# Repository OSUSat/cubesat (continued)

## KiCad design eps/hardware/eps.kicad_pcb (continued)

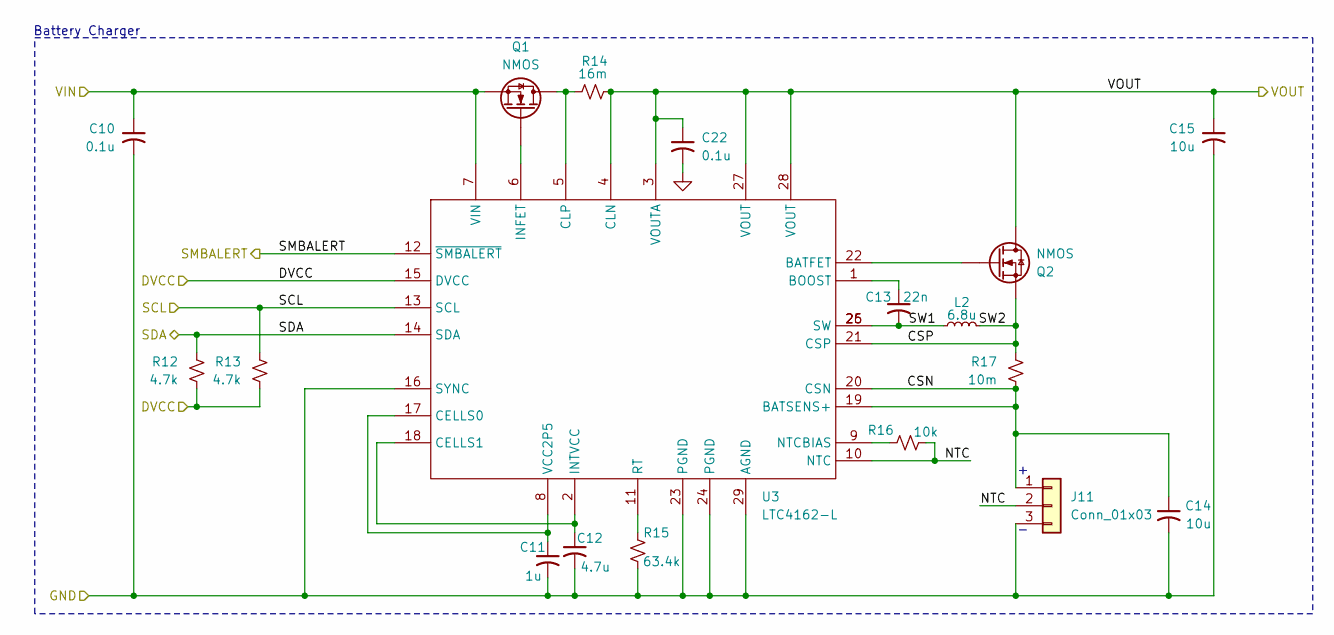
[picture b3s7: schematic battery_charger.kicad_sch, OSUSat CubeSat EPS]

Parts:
C10, C22: 0.1u; C_0402_1005Metric
C11: 1u; C_0402_1005Metric
C12: 4.7u; C_0402_1005Metric
C13: 22n; C_0402_1005Metric
C14: 10u; C_0402_1005Metric
C15: 10u; C_1206_3216Metric
J11: Conn_01x03; JST_PH_S3B-PH-K_1x03_P2.00mm_Horizontal
L2: 6.8u; L_Vishay_IHLP-2020
Q1, Q2: NMOS; TRANS_FDMC8327L
R12, R13: 4.7k; R_0402_1005Metric
R14: 16m; R_1206_3216Metric
R15: 63.4k; R_0402_1005Metric
R16: 10k; R_0402_1005Metric
R17: 10m; R_1206_3216Metric
U3: LTC4162-L; QFN-28-1EP_4x5mm_P0.5mm_EP2.65x3.65mm

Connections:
+3.3V: R12.2, R13.2, U3.15 (DVCC); also elsewhere on the board
/Battery Charger/CSN: C14.1, J11.1, R17.2, U3.19 (BATSENS+), U3.20 (CSN)
/Battery Charger/CSP: L2.2, Q2.5 (S), Q2.6 (S), Q2.7 (S), Q2.8 (S), Q2.9 (S), R17.1, U3.21 (CSP)
/Battery Charger/NTC: J11.2, R16.2, U3.10 (NTC)
/Battery Charger/SW1: C13.2, L2.1, U3.25 (SW), U3.26 (SW)
/Battery Charger/VOUT: C15.1, C22.1, Q2.1 (D), Q2.2 (D), Q2.3 (D), R14.2, U3.3 (VOUTA), U3.4 (CLN), U3.27 (VOUT), U3.28 (VOUT); also elsewhere on the board
/C1_ALERT: U3.12 (~SMBALERT); also elsewhere on the board
/C1_SCL: R13.1, U3.13 (SCL); also elsewhere on the board
/C1_SDA: R12.1, U3.14 (SDA); also elsewhere on the board
/VSYS: C10.1, Q1.5 (S), Q1.6 (S), Q1.7 (S), Q1.8 (S), Q1.9 (S), U3.7 (VIN); also elsewhere on the board
GND: C10.2, C11.2, C12.2, C14.2, C15.2, C22.2, J11.3, R15.2, U3.16 (SYNC), U3.23 (PGND), U3.24 (PGND), U3.29 (AGND); also elsewhere on the board
unnamed: Q1.4 (G), U3.6 (INFET)
unnamed: Q2.4 (G), U3.22 (BATFET)
unnamed: C13.1, U3.1 (BOOST)
unnamed: C11.1, U3.8 (VCC2P5), U3.17 (CELLS0)
unnamed: C12.1, U3.2 (INTVCC), U3.18 (CELLS1)
unnamed: Q1.1 (D), Q1.2 (D), Q1.3 (D), R14.1, U3.5 (CLP)
unnamed: R16.1, U3.9 (NTCBIAS)
unnamed: R15.1, U3.11 (RT)

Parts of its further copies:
C16, C23: 0.1u; C_0402_1005Metric
C17: 1u; C_0402_1005Metric
C18: 4.7u; C_0402_1005Metric
C19: 22n; C_0402_1005Metric
C20: 10u; C_0402_1005Metric
C21: 10u; C_1206_3216Metric
J12: Conn_01x03; JST_PH_S3B-PH-K_1x03_P2.00mm_Horizontal
L3: 6.8u; L_Vishay_IHLP-2020
Q3, Q4: NMOS; TRANS_FDMC8327L
R18, R19: 4.7k; R_0402_1005Metric
R20: 16m; R_1206_3216Metric
R21: 63.4k; R_0402_1005Metric
R22: 10k; R_0402_1005Metric
R23: 10m; R_1206_3216Metric
U4: LTC4162-L; QFN-28-1EP_4x5mm_P0.5mm_EP2.65x3.65mm

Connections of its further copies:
+3.3V: R18.2, R19.2, U4.15 (DVCC); also elsewhere on the board
/Battery Charger1/CSN: C20.1, J12.1, R23.2, U4.19 (BATSENS+), U4.20 (CSN)
/Battery Charger1/CSP: L3.2, Q4.5 (S), Q4.6 (S), Q4.7 (S), Q4.8 (S), Q4.9 (S), R23.1, U4.21 (CSP)
/Battery Charger1/NTC: J12.2, R22.2, U4.10 (NTC)
/Battery Charger1/SW1: C19.2, L3.1, U4.25 (SW), U4.26 (SW)
/Battery Charger1/VOUT: C21.1, C23.1, Q4.1 (D), Q4.2 (D), Q4.3 (D), R20.2, U4.3 (VOUTA), U4.4 (CLN), U4.27 (VOUT), U4.28 (VOUT); also elsewhere on the board
/C2_ALERT: U4.12 (~SMBALERT); also elsewhere on the board
/C2_SCL: R19.1, U4.13 (SCL); also elsewhere on the board
/C2_SDA: R18.1, U4.14 (SDA); also elsewhere on the board
/VSYS: C16.1, Q3.5 (S), Q3.6 (S), Q3.7 (S), Q3.8 (S), Q3.9 (S), U4.7 (VIN); also elsewhere on the board
GND: C16.2, C17.2, C18.2, C20.2, C21.2, C23.2, J12.3, R21.2, U4.16 (SYNC), U4.23 (PGND), U4.24 (PGND), U4.29 (AGND); also elsewhere on the board
unnamed: Q3.4 (G), U4.6 (INFET)
unnamed: Q4.4 (G), U4.22 (BATFET)
unnamed: C19.1, U4.1 (BOOST)
unnamed: C17.1, U4.8 (VCC2P5), U4.17 (CELLS0)
unnamed: C18.1, U4.2 (INTVCC), U4.18 (CELLS1)
unnamed: Q3.1 (D), Q3.2 (D), Q3.3 (D), R20.1, U4.5 (CLP)
unnamed: R22.1, U4.9 (NTCBIAS)
unnamed: R21.1, U4.11 (RT)

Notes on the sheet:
Battery Charger

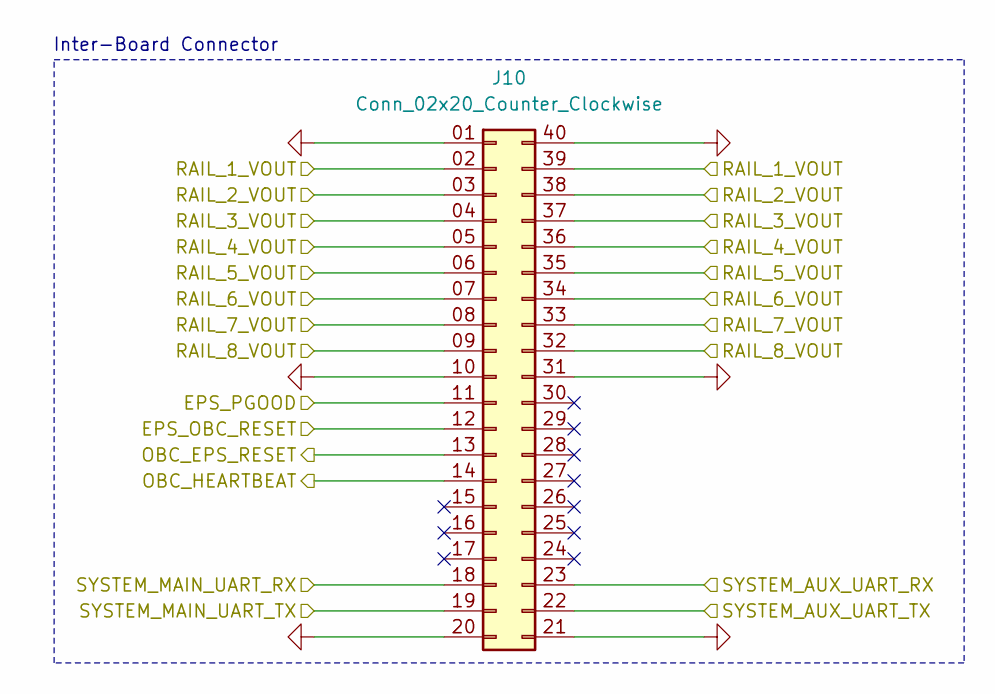
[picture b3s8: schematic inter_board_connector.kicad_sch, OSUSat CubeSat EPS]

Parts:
J10: Conn_02x20_Counter_Clockwise; SAMTEC_ERM8-020-X-X-DV

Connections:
/AUX_RX: J10.23; also elsewhere on the board
/AUX_TX: J10.22; also elsewhere on the board
/Current Monitors/RAIL_1_VOUT: J10.02 (Pin_2), J10.39; also elsewhere on the board
/Current Monitors/RAIL_2_VOUT: J10.03 (Pin_3), J10.38; also elsewhere on the board
/Current Monitors/RAIL_3_VOUT: J10.04 (Pin_4), J10.37; also elsewhere on the board
/Current Monitors/RAIL_4_VOUT: J10.05 (Pin_5), J10.36; also elsewhere on the board
/Current Monitors/RAIL_5_VOUT: J10.06 (Pin_6), J10.35; also elsewhere on the board
/Current Monitors/RAIL_6_VOUT: J10.07 (Pin_7), J10.34; also elsewhere on the board
/Current Monitors/RAIL_7_VOUT: J10.08 (Pin_8), J10.33; also elsewhere on the board
/Current Monitors/RAIL_8_VOUT: J10.09 (Pin_9), J10.32; also elsewhere on the board
/MAIN_RX: J10.18; also elsewhere on the board
/MAIN_TX: J10.19; also elsewhere on the board
/OBC_HRT: J10.14; also elsewhere on the board
/OBC_RST: J10.12; also elsewhere on the board
/PGOOD: J10.11; also elsewhere on the board
/RESET: J10.13; also elsewhere on the board
GND: J10.01 (Pin_1), J10.10, J10.20, J10.21, J10.31, J10.40; also elsewhere on the board

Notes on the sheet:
Inter-Board Connector

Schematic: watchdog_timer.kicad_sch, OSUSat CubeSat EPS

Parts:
R32: 2k; R_0402_1005Metric
U9: TPS35-Q1; SOT-23-8

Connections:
+3.3V: R32.1, U9.2 (~MR), U9.6 (WD-EN), U9.8 (VDD); also elsewhere on the board
/RESET: R32.2, U9.7 (~RESET); also elsewhere on the board
/SET0: U9.1 (SET0); also elsewhere on the board
/SET1: U9.5 (SET1); also elsewhere on the board
/WDI: U9.3 (WDI); also elsewhere on the board
GND: U9.4 (GND); also elsewhere on the board

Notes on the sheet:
The TPS3435CBHAJDDFR should be suitable.
Ensure that the open-drain RESET pin variant is selected.
Watchdog Timer

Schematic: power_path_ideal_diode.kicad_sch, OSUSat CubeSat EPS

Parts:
C133: 4.7u; C_1206_3216Metric
R119: 680k; R_0402_1005Metric
R120, R121: 100k; R_0402_1005Metric
R122, R123: 50k; R_0402_1005Metric
R124, R125, R126, R127: 470k; R_0402_1005Metric
U41: LTC4415; MSOP-16-1EP_3x4.039mm_P0.5mm_EP1.651x2.845mm

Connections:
+3.3V: R124.1, R125.1, R126.1, R127.1; also elsewhere on the board
/3v3 Voltage Regulator/VIN: C133.1, U41.9 (OUT2), U41.10 (OUT2), U41.15 (OUT1), U41.16 (OUT1); also elsewhere on the board
/Battery Charger1/VOUT: U41.7 (IN2), U41.8 (IN2); also elsewhere on the board
/Battery Charger/VOUT: R119.1, U41.1 (IN1), U41.2 (IN1); also elsewhere on the board
/D_STAT1: R124.2, U41.14 (~STAT1); also elsewhere on the board
/D_STAT2: R127.2, U41.11 (~STAT2); also elsewhere on the board
/D_WARN1: R125.2, U41.13 (~WARN1); also elsewhere on the board
/D_WARN2: R126.2, U41.12 (~WARN2); also elsewhere on the board
GND: C133.2, R121.2, R122.2, R123.2, U41.17 (GND); also elsewhere on the board
unnamed: R122.1, U41.4 (CLIM1)
unnamed: R123.1, U41.5 (CLIM2)
unnamed: R119.2, R120.1, U41.3 (EN1)
unnamed: R120.2, R121.1, U41.6 (~EN2)

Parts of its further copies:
C134: 4.7u; C_1206_3216Metric
R128: 680k; R_0402_1005Metric
R129, R130: 100k; R_0402_1005Metric
R131, R132: 50k; R_0402_1005Metric
R133, R134, R135, R136: 470k; R_0402_1005Metric
U42: LTC4415; MSOP-16-1EP_3x4.039mm_P0.5mm_EP1.651x2.845mm

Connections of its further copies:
+3.3V: R133.1, R134.1, R135.1, R136.1; also elsewhere on the board
/MPPT_V: U42.7 (IN2), U42.8 (IN2); also elsewhere on the board
/Power Path Ideal Diode1/VOUT: C134.1, U42.9 (OUT2), U42.10 (OUT2), U42.15 (OUT1), U42.16 (OUT1); also elsewhere on the board
/U_STAT1: R133.2, U42.14 (~STAT1); also elsewhere on the board
/U_STAT2: R136.2, U42.11 (~STAT2); also elsewhere on the board
/U_WARN1: R134.2, U42.13 (~WARN1); also elsewhere on the board
/U_WARN2: R135.2, U42.12 (~WARN2); also elsewhere on the board
GND: C134.2, R130.2, R131.2, R132.2, U42.17 (GND); also elsewhere on the board
unnamed: R131.1, U42.4 (CLIM1)
unnamed: R132.1, U42.5 (CLIM2)
unnamed: R128.2, R129.1, U42.3 (EN1)
unnamed: R129.2, R130.1, U42.6 (~EN2)
VBUS: R128.1, U42.1 (IN1), U42.2 (IN1); also elsewhere on the board

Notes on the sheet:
Power Path Ideal Diode

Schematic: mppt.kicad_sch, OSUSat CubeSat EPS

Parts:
C1: 47uF; C_1206_3216Metric
C2: 4.7uF; C_0402_1005Metric
C3: 1uF; C_0402_1005Metric
C4, C5: 22n; C_0402_1005Metric
C6: 4.7u; C_1206_3216Metric; Breakdown Voltage 16V
C7: 4.7u; C_0402_1005Metric; Breakdown Voltage 10V
C8, C9: 4.7u; C_0402_1005Metric; not fitted
L1: 6.8uH; L_Vishay_IHLP-2020
R10, R11: 18k; R_0402_1005Metric
U2: LTC3130-1; MSOP-16-1EP_3x4.039mm_P0.5mm_EP1.651x2.845mm

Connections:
/MPPT/MPPC: U2.8 (MPPC); also elsewhere on the board
/MPPT/VCC: C7.1, U2.7 (VCC), U2.9 (VS2)
/MPPT/VIN: C1.1, C2.1, C3.1, U2.4 (PVIN), U2.5 (VIN), U2.6 (RUN); also elsewhere on the board
/MPPT_ADC: R10.1, R11.2; also elsewhere on the board
/MPPT_V: C6.1, C8.1, C9.1, R11.1, U2.14 (VOUT); also elsewhere on the board
/PGOOD: U2.13 (PGOOD); also elsewhere on the board
GND: C1.2, C2.2, C3.2, C6.2, C7.2, C8.2, C9.2, R10.2, U2.1 (GND), U2.10 (VS1), U2.11 (MODE), U2.12 (EXTVCC), U2.17 (EPAD); also elsewhere on the board
unnamed: C4.2, U2.2 (BST1)
unnamed: C5.1, U2.15 (BST2)
unnamed: C4.1, L1.1, U2.3 (SW1)
unnamed: C5.2, L1.2, U2.16 (SW2)

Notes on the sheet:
LTC3130 Buck-Boost MPPC Controller

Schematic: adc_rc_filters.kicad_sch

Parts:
C135, C136, C137, C138, C139, C140, C141, C142, C143, C144: 100n; C_0402_1005Metric
R137, R138, R139, R140, R141, R142, R143, R144, R145, R146: 1.5k; R_0402_1005Metric

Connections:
/5V_REG_ADC: R138.1; also elsewhere on the board
/MPPT_ADC: R137.1; also elsewhere on the board
/STM32L4/5V_REG_S: C136.1, R138.2; also elsewhere on the board
/STM32L4/MPPT_S: C135.1, R137.2; also elsewhere on the board
/STM32L4/RAIL_1_S: C137.1, R139.2; also elsewhere on the board
/STM32L4/RAIL_2_S: C138.1, R140.2; also elsewhere on the board
/STM32L4/RAIL_3_S: C139.1, R141.2; also elsewhere on the board
/STM32L4/RAIL_4_S: C140.1, R142.2; also elsewhere on the board
/STM32L4/RAIL_5_S: C141.1, R143.2; also elsewhere on the board
/STM32L4/RAIL_6_S: C142.1, R144.2; also elsewhere on the board
/STM32L4/RAIL_7_S: C143.1, R145.2; also elsewhere on the board
/STM32L4/RAIL_8_S: C144.1, R146.2; also elsewhere on the board
GND: C135.2, C136.2, C137.2, C138.2, C139.2, C140.2, C141.2, C142.2, C143.2, C144.2, R139.1, R140.1, R141.1, R142.1, R143.1, R144.1, R145.1, R146.1; also elsewhere on the board

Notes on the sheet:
This gives a cutoff frequency around 1KHz
ADC RC Filters

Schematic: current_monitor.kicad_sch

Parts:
C24, C25, C29: 0.1uF; C_0402_1005Metric
C26: 1uF; C_0402_1005Metric
C27: 1uF; C_0805_2012Metric
NT1: NetTie_2; NetTie-2_SMD_Pad0.5mm
Q5, Q6: IRLML0030; SOT-23
R24, R28: 0; R_0402_1005Metric
R25: 100k; R_0402_1005Metric
R26, R27, R29: 1M; R_0402_1005Metric
TP1: TestPoint; TestPoint_Pad_D1.0mm
U5: NCS214RSQT2G; SOT-363_SC-70-6
U6: 74LVC1G07SE-7; SOT-353_SC-70-5
U7: SOT-23-6
U8: TPS22810DRVT; WSON-6-1EP_2x2mm_P0.65mm_EP1x1.6mm

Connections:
+3.3V: NT1.1, R24.1, R26.1, R27.1, R29.1, U5.3 (VS); also elsewhere on the board
/Current Monitors/OBC/RREF+: U7.5 (VREF); also elsewhere on the board
/Current Monitors/OBC/RREF-: R25.1, U7.4 (IN-); also elsewhere on the board
/Current Monitors/OBC/Shunt+: NT1.2, U5.5 (IN-); also elsewhere on the board
/Current Monitors/OBC/Shunt-: C27.2, U5.4 (IN+), U8.6 (VIN); also elsewhere on the board
/Current Monitors/RAIL_1_RST: U6.2; also elsewhere on the board
/Current Monitors/RAIL_1_VOUT: C29.2, TP1.1, U8.1 (VOUT), U8.2 (QOD); also elsewhere on the board
/STM32L4/RAIL_1_ON: R28.1, R29.2, U8.5 (EN/UVLO); also elsewhere on the board
GND: C24.2, C25.1, C26.1, C27.1, C29.1, Q5.2 (S), Q6.2 (S), R25.2, U5.1 (REF), U5.2 (GND), U5.6 (OUT), U6.3, U7.2 (VSS), U7.3 (IN+), U8.3 (CT), U8.4 (GND), U8.7 (GND); also elsewhere on the board
unnamed: Q5.3 (D), Q6.1 (G), R27.2
unnamed: C26.2, Q5.1 (G), R26.2, U6.4, U7.1
unnamed: Q6.3 (D), R28.2
unnamed: C24.1, C25.2, R24.2, U6.5, U7.6 (VDD)

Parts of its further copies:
C55, C56, C60, C63, C64, C68, C71, C72, C76, C79, C80, C84, C87, C88, C92, C95, C96, C100, C103, C104, C108: 0.1uF; C_0402_1005Metric
C57, C65, C73, C81, C89, C97, C105: 1uF; C_0402_1005Metric
C58, C66, C74, C82, C90, C98, C106: 1uF; C_0805_2012Metric
NT2, NT3, NT4, NT5, NT6, NT7, NT8: NetTie_2; NetTie-2_SMD_Pad0.5mm
Q7, Q8, Q9, Q10, Q11, Q12, Q13, Q14, Q15, Q16, Q17, Q18, Q19, Q20: IRLML0030; SOT-23
R51, R55, R59, R63, R67, R71, R75, R79, R83, R87, R91, R95, R99, R103: 0; R_0402_1005Metric
R52, R60, R68, R76, R84, R92, R100: 100k; R_0402_1005Metric
R53, R54, R56, R61, R62, R64, R69, R70, R72, R77, R78, R80, R85, R86, R88, R93, R94, R96, R101, R102, R104: 1M; R_0402_1005Metric
TP2, TP3, TP4, TP5, TP6, TP7, TP8: TestPoint; TestPoint_Pad_D1.0mm
U11, U15, U19, U23, U27, U31, U35: NCS214RSQT2G; SOT-363_SC-70-6
U12, U16, U20, U24, U28, U32, U36: 74LVC1G07SE-7; SOT-353_SC-70-5
U13, U17, U21, U25, U29, U33, U37: SOT-23-6
U14, U18, U22, U26, U30, U34, U38: TPS22810DRVT; WSON-6-1EP_2x2mm_P0.65mm_EP1x1.6mm

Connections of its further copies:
+3.3V: NT2.1, NT3.1, NT4.1, NT5.1, NT6.1, R51.1, R53.1, R54.1, R56.1, R59.1, R61.1, R62.1, R64.1, R67.1, R69.1, R70.1, R72.1, R75.1, R77.1, R78.1, R80.1, R83.1, R85.1, R86.1, R88.1, R93.1, R94.1, R96.1, R101.1, R102.1, R104.1, U11.3 (VS), U15.3 (VS), U19.3 (VS), U23.3 (VS), U27.3 (VS), U31.3 (VS), U35.3 (VS); also elsewhere on the board
+5V: NT7.1, NT8.1, R91.1, R99.1; also elsewhere on the board
/Current Monitors/Aux 1/RREF+: U25.5 (VREF); also elsewhere on the board
/Current Monitors/Aux 1/RREF-: R76.1, U25.4 (IN-); also elsewhere on the board
/Current Monitors/Aux 1/Shunt+: NT5.2, U23.5 (IN-); also elsewhere on the board
/Current Monitors/Aux 1/Shunt-: C82.2, U23.4 (IN+), U26.6 (VIN); also elsewhere on the board
/Current Monitors/Aux 2/RREF+: U29.5 (VREF); also elsewhere on the board
/Current Monitors/Aux 2/RREF-: R84.1, U29.4 (IN-); also elsewhere on the board
/Current Monitors/Aux 2/Shunt+: NT6.2, U27.5 (IN-); also elsewhere on the board
/Current Monitors/Aux 2/Shunt-: C90.2, U27.4 (IN+), U30.6 (VIN); also elsewhere on the board
/Current Monitors/Auxiliary & Deployables/RREF+: U37.5 (VREF); also elsewhere on the board
/Current Monitors/Auxiliary & Deployables/RREF-: R100.1, U37.4 (IN-); also elsewhere on the board
/Current Monitors/Auxiliary & Deployables/Shunt+: NT8.2, U35.5 (IN-); also elsewhere on the board
/Current Monitors/Auxiliary & Deployables/Shunt-: C106.2, U35.4 (IN+), U38.6 (VIN); also elsewhere on the board
/Current Monitors/Comms/RREF+: U13.5 (VREF); also elsewhere on the board
/Current Monitors/Comms/RREF-: R52.1, U13.4 (IN-); also elsewhere on the board
/Current Monitors/Comms/Shunt+: NT2.2, U11.5 (IN-); also elsewhere on the board
/Current Monitors/Comms/Shunt-: C58.2, U11.4 (IN+), U14.6 (VIN); also elsewhere on the board
/Current Monitors/GPS/RREF+: U21.5 (VREF); also elsewhere on the board
/Current Monitors/GPS/RREF-: R68.1, U21.4 (IN-); also elsewhere on the board
/Current Monitors/GPS/Shunt+: NT4.2, U19.5 (IN-); also elsewhere on the board
/Current Monitors/GPS/Shunt-: C74.2, U19.4 (IN+), U22.6 (VIN); also elsewhere on the board
/Current Monitors/RAIL_2_RST: U12.2; also elsewhere on the board
/Current Monitors/RAIL_2_VOUT: C60.2, TP2.1, U14.1 (VOUT), U14.2 (QOD); also elsewhere on the board
/Current Monitors/RAIL_3_RST: U16.2; also elsewhere on the board
/Current Monitors/RAIL_3_VOUT: C68.2, TP3.1, U18.1 (VOUT), U18.2 (QOD); also elsewhere on the board
/Current Monitors/RAIL_4_RST: U20.2; also elsewhere on the board
/Current Monitors/RAIL_4_VOUT: C76.2, TP4.1, U22.1 (VOUT), U22.2 (QOD); also elsewhere on the board
/Current Monitors/RAIL_5_RST: U24.2; also elsewhere on the board
/Current Monitors/RAIL_5_VOUT: C84.2, TP5.1, U26.1 (VOUT), U26.2 (QOD); also elsewhere on the board
/Current Monitors/RAIL_6_RST: U28.2; also elsewhere on the board
/Current Monitors/RAIL_6_VOUT: C92.2, TP6.1, U30.1 (VOUT), U30.2 (QOD); also elsewhere on the board
/Current Monitors/RAIL_7_RST: U32.2; also elsewhere on the board
/Current Monitors/RAIL_7_VOUT: C100.2, TP7.1, U34.1 (VOUT), U34.2 (QOD); also elsewhere on the board
/Current Monitors/RAIL_8_RST: U36.2; also elsewhere on the board
/Current Monitors/RAIL_8_VOUT: C108.2, TP8.1, U38.1 (VOUT), U38.2 (QOD); also elsewhere on the board
/Current Monitors/Raspberry Pi Camera/RREF+: U33.5 (VREF); also elsewhere on the board
/Current Monitors/Raspberry Pi Camera/RREF-: R92.1, U33.4 (IN-); also elsewhere on the board
/Current Monitors/Raspberry Pi Camera/Shunt+: NT7.2, U31.5 (IN-); also elsewhere on the board
/Current Monitors/Raspberry Pi Camera/Shunt-: C98.2, U31.4 (IN+), U34.6 (VIN); also elsewhere on the board
/Current Monitors/Sensors/RREF+: U17.5 (VREF); also elsewhere on the board
/Current Monitors/Sensors/RREF-: R60.1, U17.4 (IN-); also elsewhere on the board
/Current Monitors/Sensors/Shunt+: NT3.2, U15.5 (IN-); also elsewhere on the board
/Current Monitors/Sensors/Shunt-: C66.2, U15.4 (IN+), U18.6 (VIN); also elsewhere on the board
/STM32L4/RAIL_2_ON: R55.1, R56.2, U14.5 (EN/UVLO); also elsewhere on the board
/STM32L4/RAIL_3_ON: R63.1, R64.2, U18.5 (EN/UVLO); also elsewhere on the board
/STM32L4/RAIL_4_ON: R71.1, R72.2, U22.5 (EN/UVLO); also elsewhere on the board
/STM32L4/RAIL_5_ON: R79.1, R80.2, U26.5 (EN/UVLO); also elsewhere on the board
/STM32L4/RAIL_6_ON: R87.1, R88.2, U30.5 (EN/UVLO); also elsewhere on the board
/STM32L4/RAIL_7_ON: R95.1, R96.2, U34.5 (EN/UVLO); also elsewhere on the board
/STM32L4/RAIL_8_ON: R103.1, R104.2, U38.5 (EN/UVLO); also elsewhere on the board
GND: C55.2, C56.1, C57.1, C58.1, C60.1, C63.2, C64.1, C65.1, C66.1, C68.1, C71.2, C72.1, C73.1, C74.1, C76.1, C79.2, C80.1, C81.1, C82.1, C84.1, C87.2, C88.1, C89.1, C90.1, C92.1, C95.2, C96.1, C97.1, C98.1, C100.1, C103.2, C104.1, C105.1, C106.1, C108.1, Q7.2 (S), Q8.2 (S), Q9.2 (S), Q10.2 (S), Q11.2 (S), Q12.2 (S), Q13.2 (S), Q14.2 (S), Q15.2 (S), Q16.2 (S), Q17.2 (S), Q18.2 (S), Q19.2 (S), Q20.2 (S), R52.2, R60.2, R68.2, R76.2, R84.2, R92.2, R100.2, U11.1 (REF), U11.2 (GND), U11.6 (OUT), U12.3, U13.2 (VSS), U13.3 (IN+), U14.3 (CT), U14.4 (GND), U14.7 (GND), U15.1 (REF), U15.2 (GND), U15.6 (OUT), U16.3, U17.2 (VSS), U17.3 (IN+), U18.3 (CT), U18.4 (GND), U18.7 (GND), U19.1 (REF), U19.2 (GND), U19.6 (OUT), U20.3, U21.2 (VSS), U21.3 (IN+), U22.3 (CT), U22.4 (GND), U22.7 (GND), U23.1 (REF), U23.2 (GND), U23.6 (OUT), U24.3, U25.2 (VSS), U25.3 (IN+), U26.3 (CT), U26.4 (GND), U26.7 (GND), U27.1 (REF), U27.2 (GND), U27.6 (OUT), U28.3, U29.2 (VSS), U29.3 (IN+), U30.3 (CT), U30.4 (GND), U30.7 (GND), U31.1 (REF), U31.2 (GND), U31.6 (OUT), U32.3, U33.2 (VSS), U33.3 (IN+), U34.3 (CT), U34.4 (GND), U34.7 (GND), U35.1 (REF), U35.2 (GND), U35.6 (OUT), U36.3, U37.2 (VSS), U37.3 (IN+), U38.3 (CT), U38.4 (GND), U38.7 (GND); also elsewhere on the board
unnamed: Q7.3 (D), Q8.1 (G), R54.2
unnamed: C57.2, Q7.1 (G), R53.2, U12.4, U13.1
unnamed: Q8.3 (D), R55.2
unnamed: C65.2, Q9.1 (G), R61.2, U16.4, U17.1
unnamed: Q10.3 (D), R63.2
unnamed: Q9.3 (D), Q10.1 (G), R62.2
unnamed: Q11.3 (D), Q12.1 (G), R70.2
unnamed: C73.2, Q11.1 (G), R69.2, U20.4, U21.1
unnamed: Q12.3 (D), R71.2
unnamed: Q13.3 (D), Q14.1 (G), R78.2
unnamed: C81.2, Q13.1 (G), R77.2, U24.4, U25.1
unnamed: Q14.3 (D), R79.2
unnamed: Q15.3 (D), Q16.1 (G), R86.2
unnamed: C89.2, Q15.1 (G), R85.2, U28.4, U29.1
unnamed: Q16.3 (D), R87.2
unnamed: Q17.3 (D), Q18.1 (G), R94.2
unnamed: C97.2, Q17.1 (G), R93.2, U32.4, U33.1
unnamed: Q18.3 (D), R95.2
unnamed: Q19.3 (D), Q20.1 (G), R102.2
unnamed: C105.2, Q19.1 (G), R101.2, U36.4, U37.1
unnamed: Q20.3 (D), R103.2
unnamed: C55.1, C56.2, R51.2, U12.5, U13.6 (VDD)
unnamed: C63.1, C64.2, R59.2, U16.5, U17.6 (VDD)
unnamed: C71.1, C72.2, R67.2, U20.5, U21.6 (VDD)
unnamed: C79.1, C80.2, R75.2, U24.5, U25.6 (VDD)
unnamed: C87.1, C88.2, R83.2, U28.5, U29.6 (VDD)
unnamed: C95.1, C96.2, R91.2, U32.5, U33.6 (VDD)
unnamed: C103.1, C104.2, R99.2, U36.5, U37.6 (VDD)

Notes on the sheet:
Open-drain output
Reference setting resistor placed between these two pins.
Shunt resistor placed between these two pins. Also, use a copper pour between the load.
For this application, we likely want the 1.2V package for the current monitor IC.
Credit to https://github.com/rgw3d/1KCubeSat_Hardware
18V, 3A Max Input/Output
Load Switch
Monostable Pulldown
Input Reset Buffer
Current Monitor

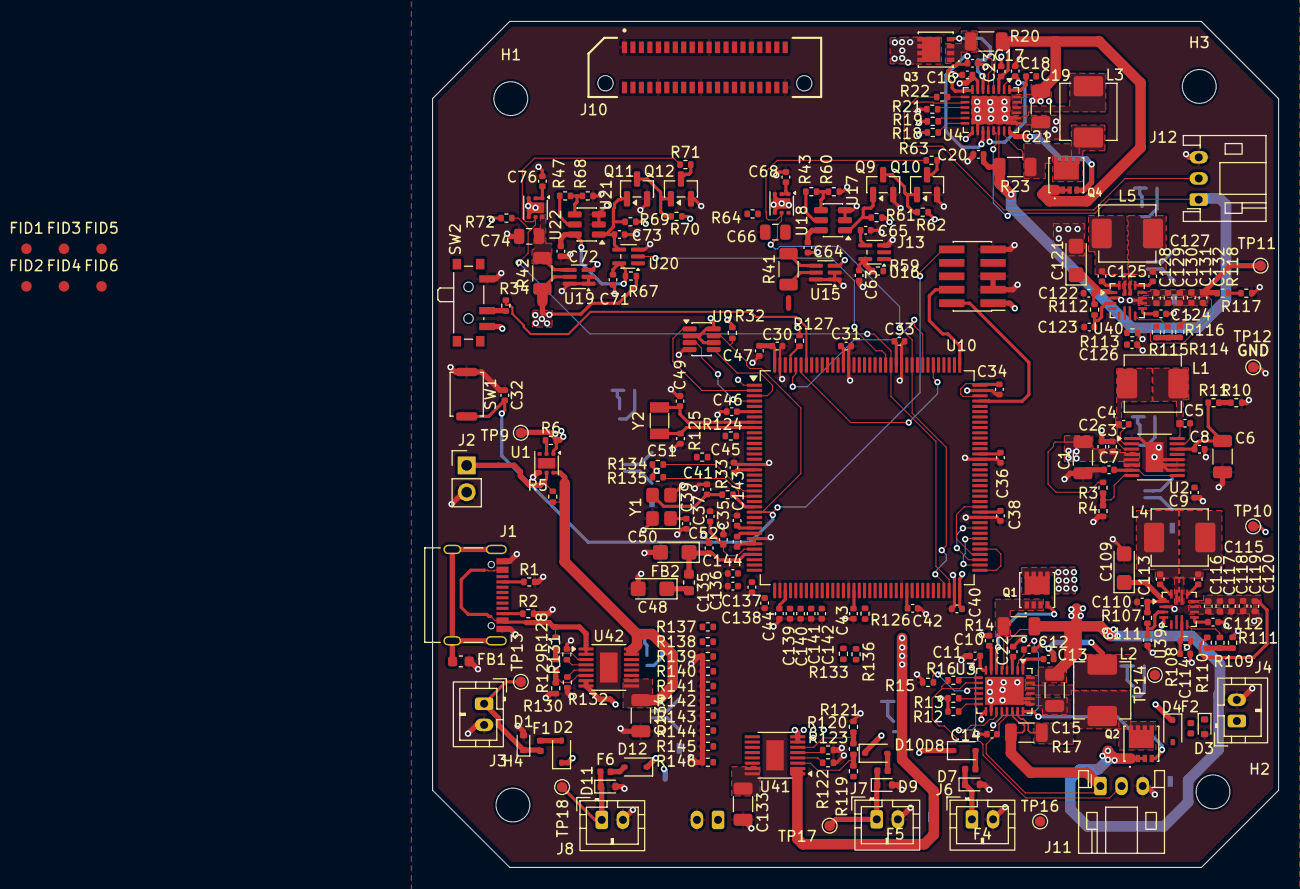
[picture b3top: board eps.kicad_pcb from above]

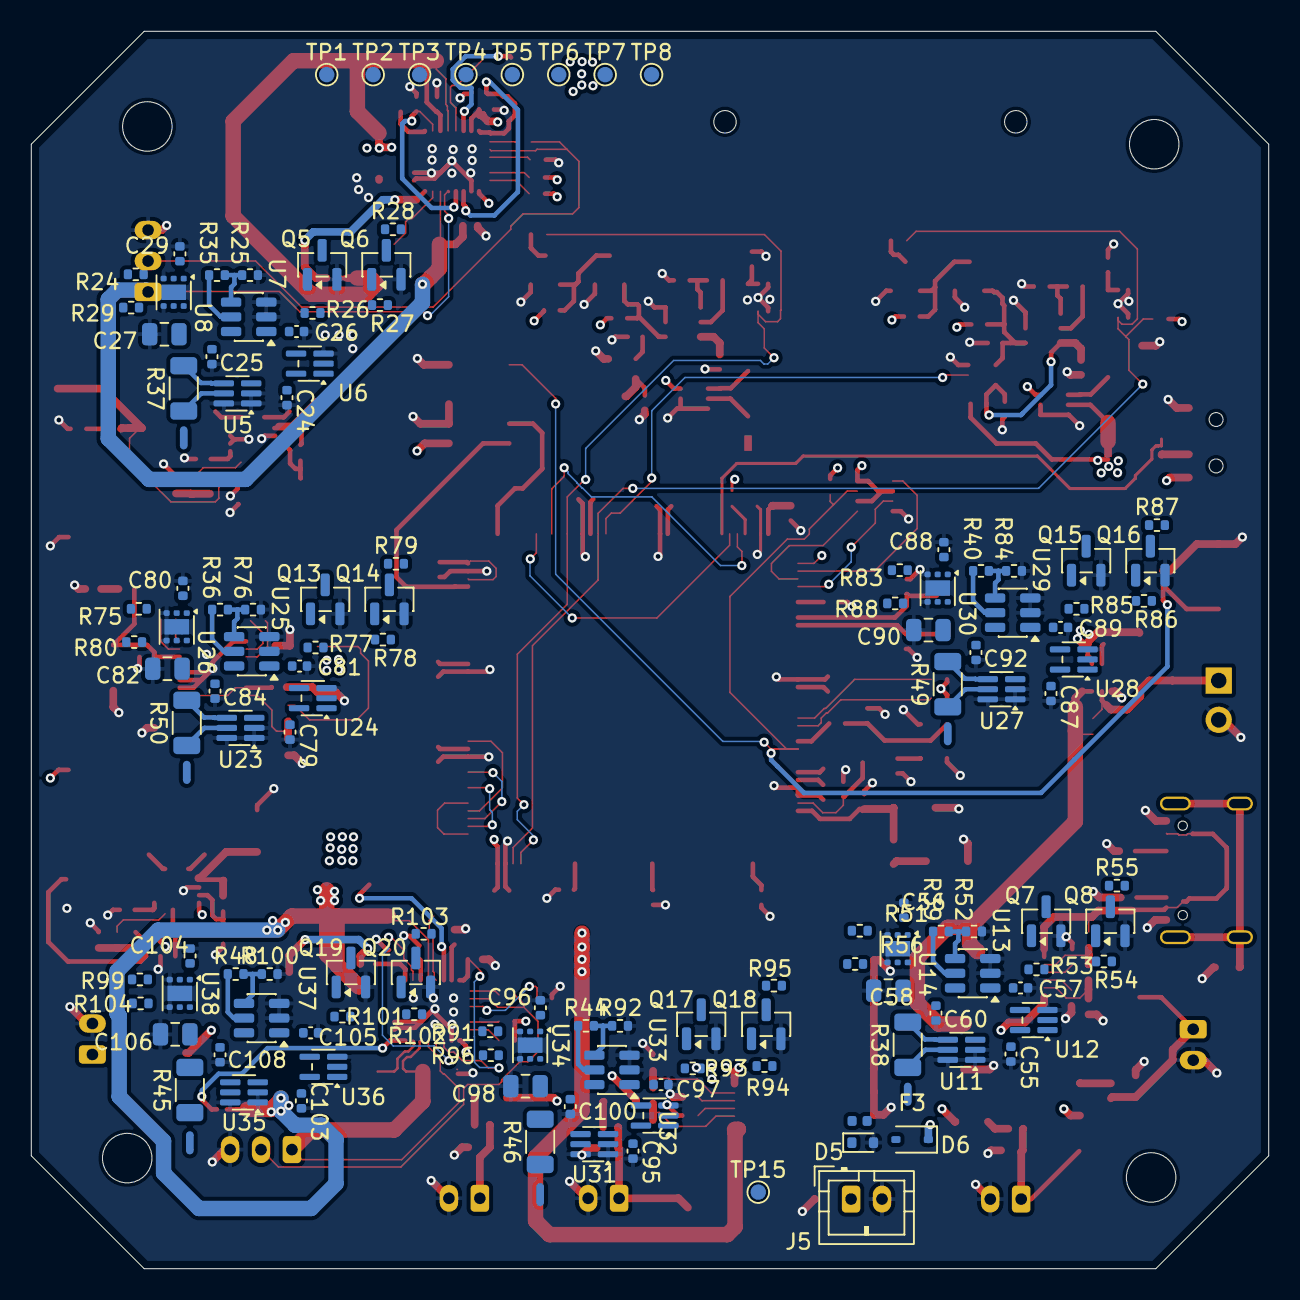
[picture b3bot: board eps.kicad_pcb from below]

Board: 6 copper layers, 80.0 x 80.0 mm, 388 parts (133 on the bottom side), 226 nets.
